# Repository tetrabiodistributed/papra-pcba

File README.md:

# PAPRA Printed Circuit Board Assembly (PCBA)

PAPRa PCBA - printed circuit board assembly for the PAPRa M12 Controller

Full documentation page for building the PAPRa can be found here: https://tetrabiodistributed.github.io/papra/

Firmware for flashing the PAPRA PCBA can be found here: https://github.com/tetrabiodistributed/papra-pcb-firmware/tree/main/papracode

## PAPRa PCBA comes in 2 form factors

### Thru Hole Technology

* Part Number A-TET-001113
* Suitable for hand soldering
* Larger form factor
* Easy to assemble, intended for novice 
* BOM parts should be easy to source
* Uses Adafruit QT PY or Seeed Xiao microcontroller board
* Firmware: TBD

### SMT

* Part Number A-TET-001100
* Suitable for mass production
* Smallest form factor
* Machine assembly recommended, very difficult to hand solder
* Lowest BOM cost
* Uses ATTINY 0/1/2-Series 14pin SOIC
* Firmware found here: https://github.com/tetrabiodistributed/papra-pcb-firmware/tree/main/papracode

## Notes for programming

* Make a UPDI Programmer: https://create.arduino.cc/projecthub/john-bradnam/create-your-own-updi-programmer-1e55f1?ref=user&ref_id=466812&offset=6
* The board features a UPDI header on the top left of the PCB (top being the side with the battery connectors) the pins are top to bottom 5V, GND and data. 
* Setup Arduino: https://www.hackster.io/john-bradnam/using-the-new-attiny-processors-with-arduino-ide-612185
* You will need to use the megaTinyCore library by SpenceKonde: https://github.com/SpenceKonde/megaTinyCore

Upload settings can be found in the arduino program. 

Please note that there are a number of ATTiny SKUs that are compatible with this PCB and code, please refer to the below table when choosing an appropriate IC.

| Model number   | Confirmed   | Notes                             |
| -------------- | ----------- | --------------------------------- |
| ATtiny204SSN_, | Yes         | See Below(1)  |
| ATtiny404SSN_, | Yes         |    	                           |
| ATtiny804SSN_, | Yes         |                                   |
| ATtiny1604SSN_,| Yes         |    	                           |
| ATtiny214SSN_, | Yes         | See Below(1)  |
| ATtiny414SSN_, | Yes         |    	                           |
| ATtiny814SSN_, | Yes         |                                   |
| ATtiny1614SSN_,| Yes         |    	                           |
| ATtiny1624SSU, | Yes         |    	                           |

(1)ATtiny 204 and 214 have limited (2K) flash memory for program space, but the firmware can be made to fit by sacraficing the bootup LED sequence.

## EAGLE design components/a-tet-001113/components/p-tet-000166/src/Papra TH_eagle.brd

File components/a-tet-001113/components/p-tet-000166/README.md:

# P-TET-000166 — PAPRa M12 Controller PCB (through-hole)

## Files

| Path | What |
|---|---|
| `src/Papra TH_eagle.sch`, `src/Papra TH_eagle.brd` | Original Eagle 9.6.2 design. Source of truth for the migration. |
| `src/papra-pcb-th/` | KiCad 10 project **generated** from the Eagle files by `make import`. Do not hand-edit until the Eagle files are retired; regenerate instead. |
| `src/papra-pcb-th/papra-pcb-th.pretty/`, `papra-pcb-th.kicad_sym` | Project footprint/symbol libraries extracted from the Eagle design. |
| `src/papra-pcb-th/3d/` | Manufacturer STEP models (see `3d/SOURCES.md`). |
| `dist/Papra TH_eagle_2023-03-08.zip` | Gerbers Eagle produced for the fab run. The Gerber check compares against these. |
| `../../lcsc-parts.csv` | LCSC numbers looked up for the BOM MPNs (`make lcsc`). |

## How the migration is validated (`make check`, from the repo root)

1. **Board structure** (`checks/test_board.py`): every Eagle element is a KiCad footprint with the
   same value, position, side; every pad has the same position, drill and copper size; every
   net has the same pads; the GND pour survived.
2. **Schematic** (`checks/test_schematic.py`): KiCad's own netlister reproduces Eagle's nets pad
   for pad; ERC has no errors; KiCad's schematic-parity DRC agrees board with schematic; the
   board passes the design rules translated from Eagle's `.brd`.
3. **Fab output** (`checks/test_gerbers.py`): Gerbers plotted from the KiCad board are rendered
   and XOR-compared per layer against the 2023 Eagle Gerbers; the drill files must list
   identical holes. Overlays land in `build/p-tet-000166/render/diff-<layer>.png`.
4. **3D placement** (`checks/test_models.py`): every model is placed with KiCad's own model
   transform (`checks/model_geom.py`, the matrix chain from the 3D viewer, on the geometry
   KiCad loads from the STEP file) and must sit on its side of the board with only its pins
   through it, landing on its pads. Manufacturer parts are held to datasheet numbers in
   `checks/parts.py` `PLACEMENT` (height, pin length, footprint, which way it faces).
5. **Determinism** (`checks/test_project.py`): a re-import of unchanged sources gives
   byte-identical files. kicad-cli and pcbnew mint random UUIDs and write elements in memory
   order; `checks/stable_ids.py` renames UUIDs by ordinal and sorts the board's blocks.

Known, accepted differences are listed in `checks/config.py` and `checks/project.py`.

## Regenerating

```
make import     # Eagle -> KiCad (board via kicad-cli, schematic via checks/sch_convert.py)
make check
make outputs    # ERC/DRC reports, PDFs, BOMs, Gerbers, drills, STEP, renders in build/
```

## Working in the KiCad GUI

- Open `src/papra-pcb-th/papra-pcb-th.kicad_pro`, not the `.kicad_sch` or `.kicad_pcb` on
  their own. The project carries the symbol/footprint library tables and the DRC/ERC
  severities; opened standalone, KiCad reports every library as missing and uses its
  default rules.
- Close KiCad before `make import`. KiCad keeps the project settings in memory and writes
  them back on save, which silently reverts the generated `.kicad_pro`.

## Additions over the Eagle design

- **Plated slots for the DC jack.** Eagle emulated the PJ-066A blade slots with pads, end
  holes and milling; the KiCad board has one plated oval pad per blade (`checks/parts.py`
  `SLOT_PADS`), which is what the fab produces and what DRC can reason about.
- **QR code on the bottom silkscreen** linking to https://tetrab.io, generated by
  `checks/qr.py` (content and module size in `checks/parts.py`) and placed automatically in
  the largest area free of holes, pads and other silkscreen. It is excluded from the Gerber
  comparison against the 2023 Eagle output, as are the slot pads.
- **3D models.** Standard parts use the models shipped with KiCad. The FASTON tabs, BNC,
  potentiometer and XIAO use manufacturer STEP files under `src/papra-pcb-th/3d/`
  (`3d/SOURCES.md`); their rotation and offset were solved, not eyeballed, by
  `checks/model_solve.py` from the model geometry and the datasheet rules, and are pinned in
  `checks/models.py`. The DC jack is drawn with KiCad's PJ-063AH model because Same Sky
  publishes none for the PJ-066A. To re-solve after changing a model or a rule:

  ```
  .venv/bin/python -m checks.model_solve POT1 H2 BATT+0 U1
  ```

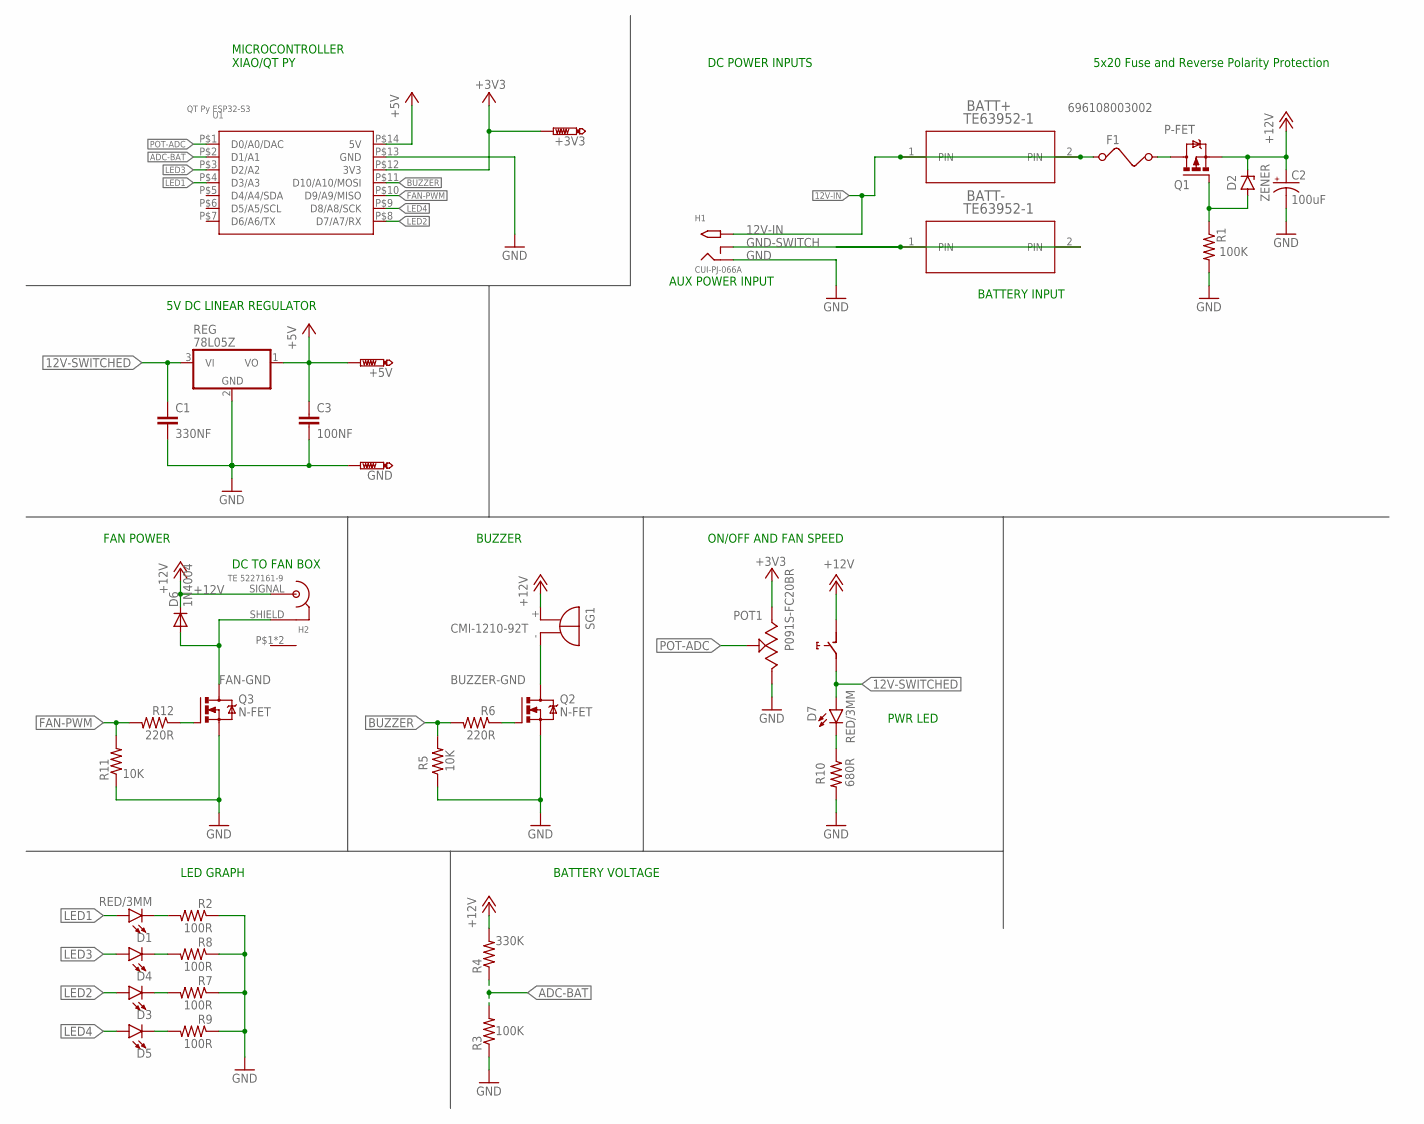
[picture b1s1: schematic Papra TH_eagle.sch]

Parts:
+3V3, +5V: PTR1PAD1-17; P1-17
BATT+: TE63952-1
BATT-: TE63952-1
C1: 330NF; CAP-PTH-SMALL-KIT
C2: 100uF; CPOL-RADIAL-2.5MM-6.5MM
C3: 100NF; CAP-PTH-SMALL-KIT
D1, D3, D4, D5, D7: RED/3MM; LED_3MM
D2: ZENER; DIODE-AXIAL
D6: 1N4004; DO41-10
F1: 696108003002; FUSE
GND: PTR1PAD1-17; P1-17
H1: CUI-PJ-066A; DCJACK-PJ-066A-SLOT
H2: TE 5227161-9; TE-BNC
POT1: P091S-FC20BR
Q1: P-FET; TO220BV
Q2, Q3: N-FET; TO220BV
R1, R3: 100K; 0207/10
R2, R7, R8, R9: 100R; 0207/10
R4: 330K; 0207/10
R5, R11: 10K; 0207/10
R6, R12: 220R; 0207/10
R10: 680R; 0207/10
REG: 78L05Z; TO92
SG1: CMI-1210-92T; F/TMB
U1: QT Py ESP32-S3; MODULE14P-TH+PAD

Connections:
12V-IN: BATT+.1, BATT+.2, F1.1, H1.PWR (TIP), H1.PWR$1 (TIP), H1.PWR$2 (TIP), H1.PWR$3 (TIP)
12V-IN-FUSED: F1.2, Q1.D
12V-IN-GATE: D2.1 (A), Q1.G, R1.1
12V-SWITCHED: C1.1, D7.A, POT1.NO (5), REG.3 (VI)
+3V3: +3V3.TP, POT1.3, U1.P$12 (3V3)
+5V: +5V.TP, C3.1, REG.1 (VO), U1.P$14 (5V)
+12V: C2.1 (+), D2.2 (C), D6.C, H2.SIGNAL (P1), POT1.COM (4), Q1.S, R4.2, SG1.+
ADC-BAT: R3.2, R4.1, U1.P$2 (D1/A1)
BUZZER: R5.2, R6.2, U1.P$11 (D10/A10/MOSI)
BUZZER-GND: Q2.D, SG1.-
FAN-GND: D6.A, H2.SHIELD (P2), Q3.D
FAN-PWM: R11.2, R12.2, U1.P$10 (D9/A9/MISO)
FETGATE: Q3.G, R12.1
FETGATE1: Q2.G, R6.1
GND: C1.2, C2.2 (-), C3.2, GND.TP, H1.GND (RING), H1.GND$1 (RING), H1.GND$2 (RING), H1.GND$3 (RING), POT1.1, Q2.S, Q3.S, R1.2, R2.1, R3.1, R5.1, R7.1, R8.1, R9.1, R10.2, R11.1, REG.2 (GND), U1.P$13 (GND)
GND-SWITCH: BATT-.1, BATT-.2, H1.GNDBREAK (RING_SW), H1.GNDBREAK$1 (RING_SW), H1.GNDBREAK$2 (RING_SW), H1.GNDBREAK$3 (RING_SW)
LED1: D1.A, U1.P$4 (D3/A3)
LED1.R: D1.K (C), R2.2
LED2: D3.A, U1.P$8 (D7/A7/RX)
LED2.R: D4.K (C), R8.2
LED3: D4.A, U1.P$3 (D2/A2)
LED3.R: D3.K (C), R7.2
LED4: D5.A, U1.P$9 (D8/A8/SCK)
LED4.R: D5.K (C), R9.2
LED5-R: D7.K (C), R10.1
POT-ADC: POT1.2, U1.P$1 (D0/A0/DAC)

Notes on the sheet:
AUX POWER INPUT
BATTERY INPUT
5x20 Fuse and Reverse Polarity Protection
5V DC LINEAR REGULATOR
ON/OFF AND FAN SPEED
FAN POWER
MICROCONTROLLER XIAO/QT PY
LED GRAPH
BATTERY VOLTAGE
DC TO FAN BOX
PWR LED
BUZZER
DC POWER INPUTS

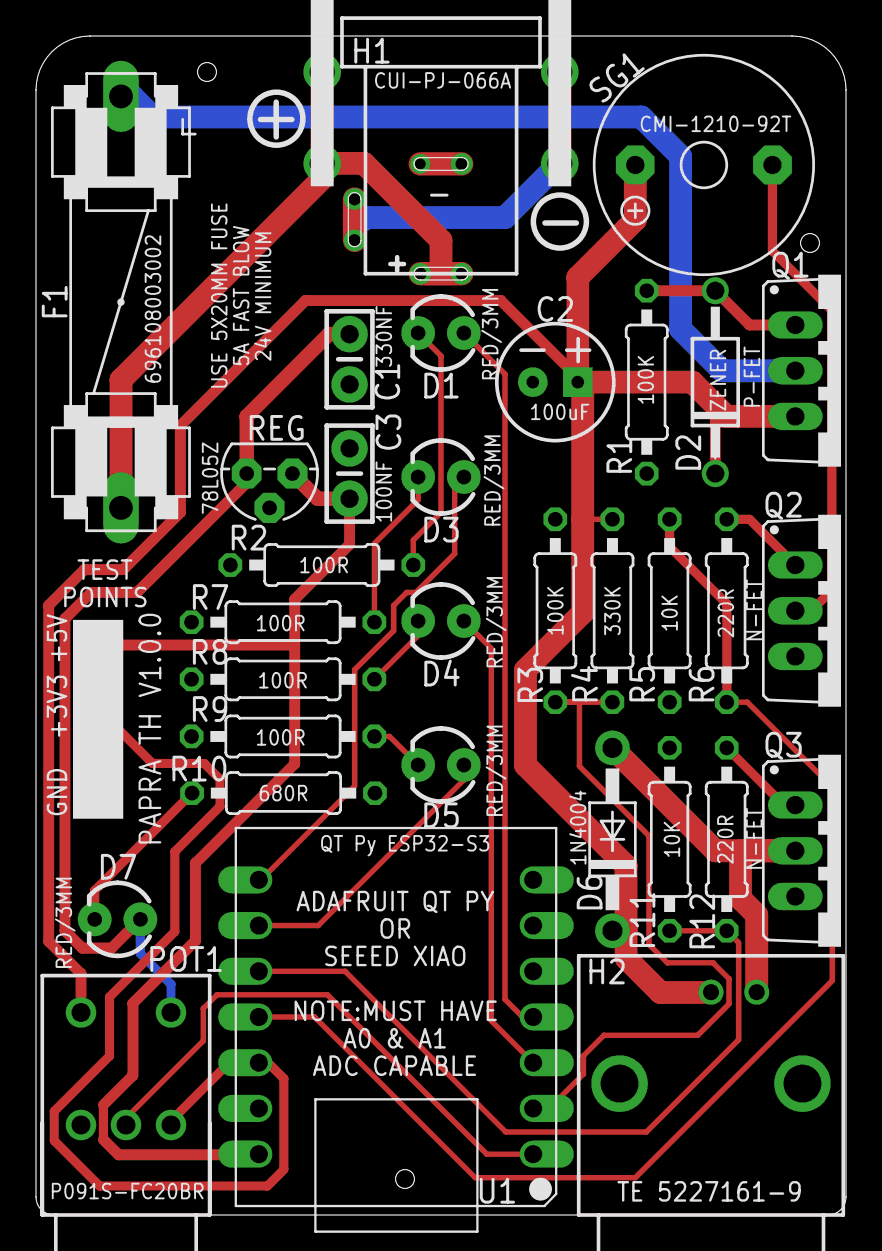
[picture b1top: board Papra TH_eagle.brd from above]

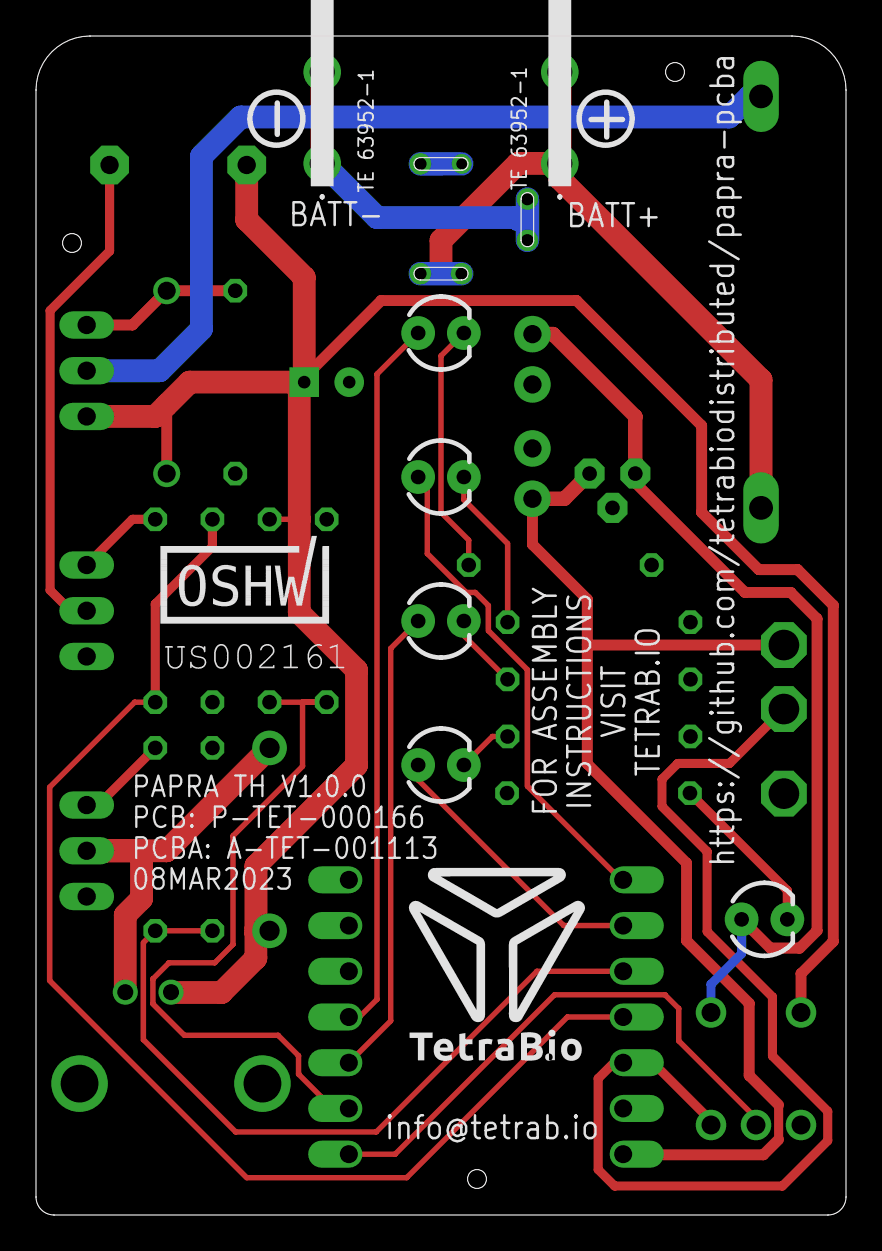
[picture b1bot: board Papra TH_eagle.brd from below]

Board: 2 copper layers, 45.0 x 65.5 mm, 37 parts (2 on the bottom side), 26 nets.

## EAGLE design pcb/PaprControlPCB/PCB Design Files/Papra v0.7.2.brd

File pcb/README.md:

The Tetra PAPRA project requires 1 PCBA, v.7 or newer.

PaprControlPCB - this is a speed controller that allows for adjusting speed of blower

Note:
A PCB is a bare board.
A PCBA is an assembly of a PCB and OTS (off the shelf) components, which are typically a mix of surface mount and thru-hole components.

PCBA Bring-Up Instructions:

1. Connect power to the board via 2.5mm DC jack (H1) using 12V Nominal (7V min, 14V max) DC power, ideally current limitable. Do not connect fan to the output connector at this time.

* Note DC polarity on connector is important, center pin is positive.
   * Insertion length on connector is 8.4mm, so body of mating jack should be at least this length.
   * For use with a bench power supply, a cut-end cable option is [Tensility CA-2185](https://www.digikey.com/en/products/detail/tensility-international-corp/CA-2185/568576) 
   * For a standalone power adapter, consider a [Tri-Mag L6R06H-120 12V/6W supply](https://www.digikey.com/en/products/detail/tri-mag-llc/L6R06H-120/7682617)
2. For adjustable power supply, set the voltage to12V and set initial current limit to ~25mA, which should be sufficient to power up processor and drive LEDs.
3. Turn the potentiometer/switch (POT1) to ON. 

4. Confirm the power LED (LED5) illuminates with 12V power.

5. Measure 5V regulator (U1) is outputting 5VDC. This can be inspected with a voltmeter measuring the UDPI header as follows:
   * Pin 2 is GND
   * Pin 3 is +5V
6. At this point, the board is powered and ready for programming via UPDI. Follow the instructions [here.](https://github.com/tetrabiodistributed/PAPRA-PCB/blob/main/README.md).
7. Upon successful completion of firmware installation, confirm the board powers up and the 4 LEDs (LED1 - LED4) light up at boot up in a sequence.
8. For boards with the buzzer installed, confirm the buzzer chirps at bootup.
9. In preparation for testing with a DC blower and battery, disconnect the DC jack from H1.
10. Source a fully charged [Milwaukee M12 Red Lithium Battery 48-11-2401](https://www.milwaukeetool.com/Products/Batteries-and-Chargers/M12-Batteries-and-Chargers/48-11-2401) or similar. 
11. Connect DC power to BNC connector (H2).
* WARNING: If the board is not installed in the battery housing, pay careful attention to the polarity
12. Turn on potentiometer (POT1) and adjust the fan speed from high to low, which checking the DC blower is working and speed is changing with potentiometer adjustments.

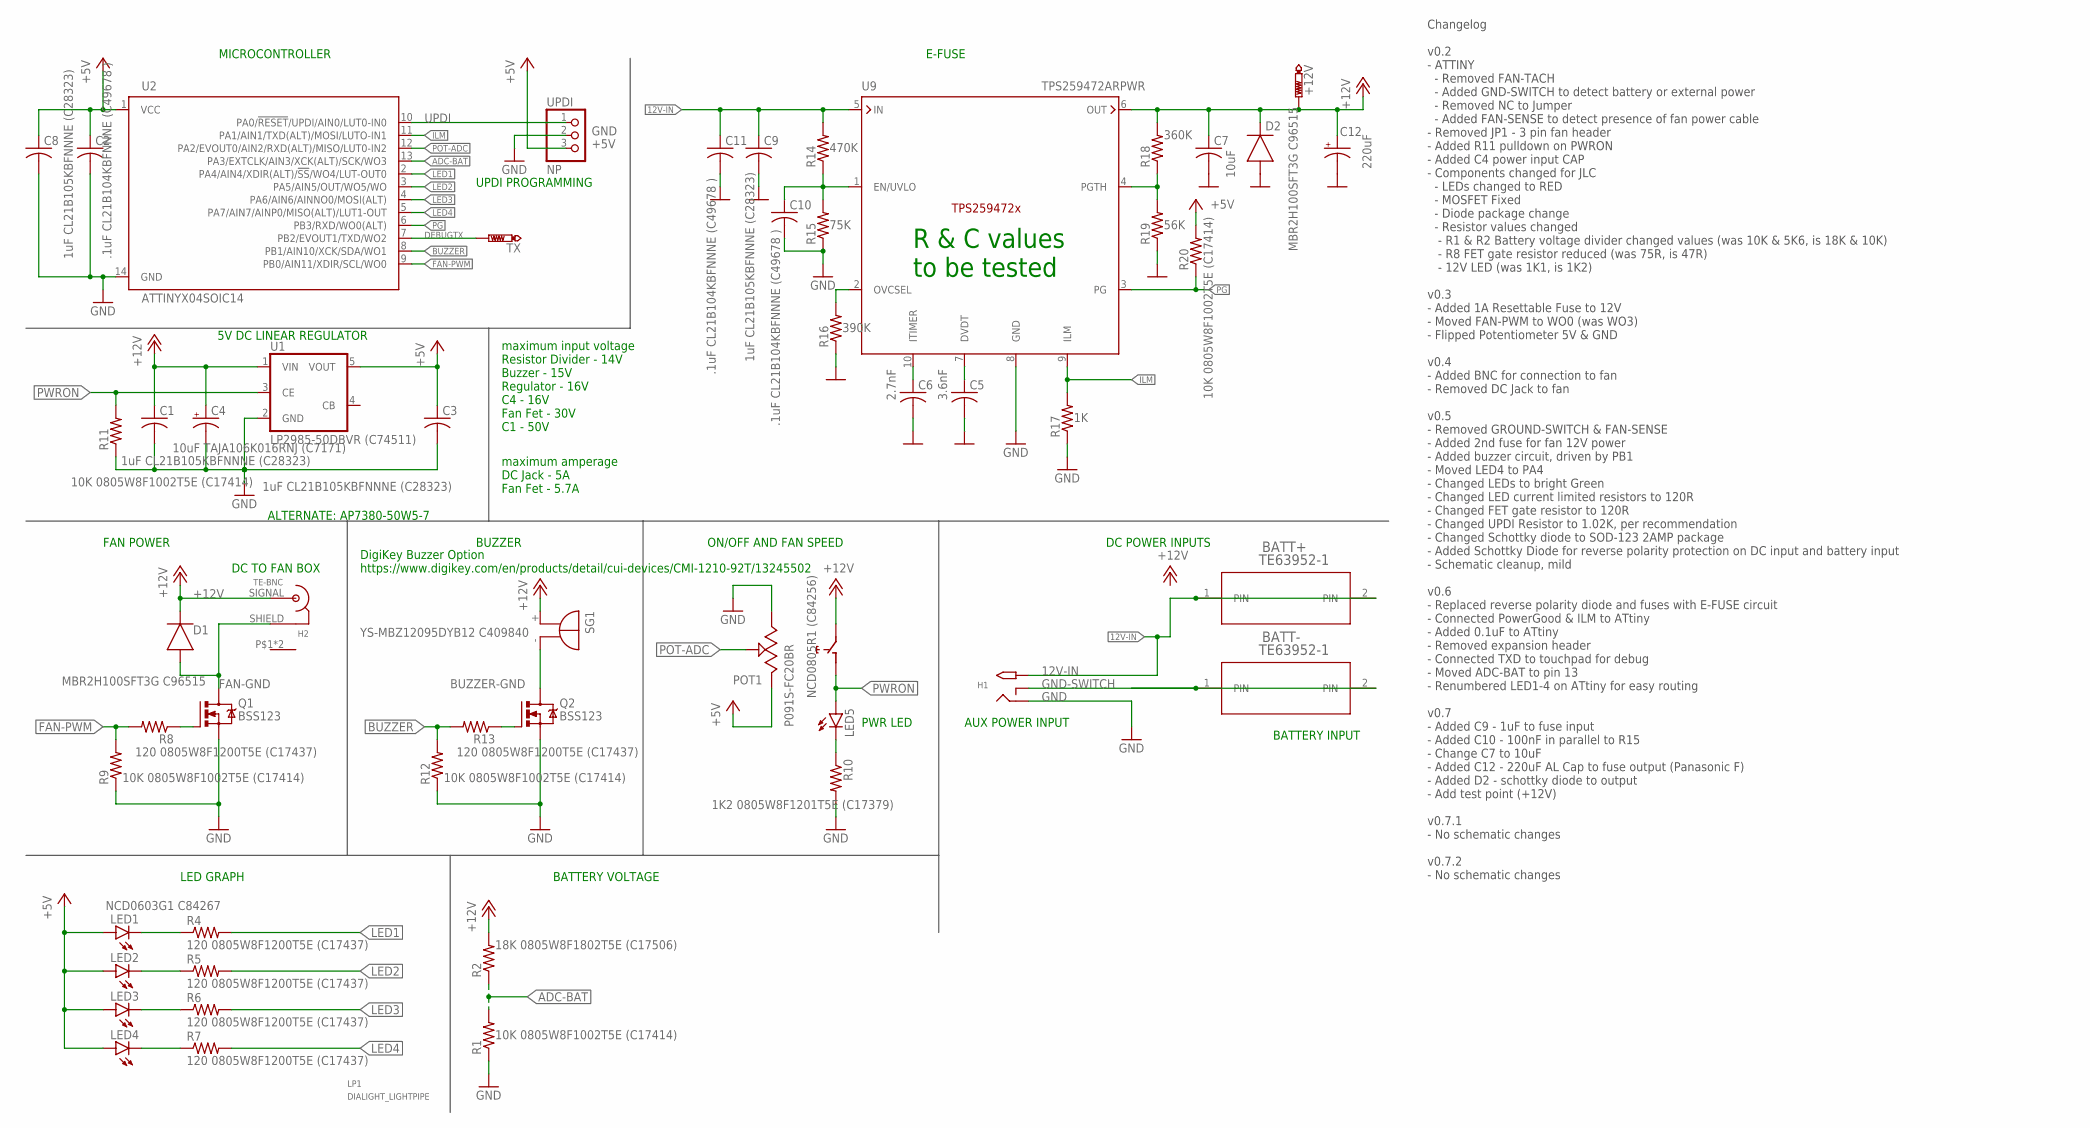
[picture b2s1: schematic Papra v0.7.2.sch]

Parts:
+12V: PTR1B1,27; B1,27
BATT+: TE63952-1
BATT-: TE63952-1
C1, C3, C8, C11: 1uF CL21B105KBFNNNE (C28323); C0805
C2, C9, C10: .1uF CL21B104KBFNNNE (C49678 ); C0805
C4: 10uF TAJA106K016RNJ (C7171); A/3216-18R
C5: 3.6nF; C0805
C6: 2.7nF; C0805
C7: 10uF; C0805
C12: 220uF; PANASONIC_F
D1, D2: MBR2H100SFT3G C96515; SODFL3718X115
H1: M-CUI-PJ-066A; DCJACK-PJ-066A
H2: TE-BNC
LED1, LED2, LED3, LED4: NCD0603G1 C84267; CHIPLED_0805
LED5: NCD0805R1 (C84256); CHIPLED_0805
LP1: DIALIGHT_LIGHTPIPE; DIALIGHT_5151020F_/LEDS
POT1: P091S-FC20BR
Q1, Q2: BSS123; SOT23
R1, R9, R11, R12, R20: 10K 0805W8F1002T5E (C17414); R0805
R2: 18K 0805W8F1802T5E (C17506); R0805
R4, R5, R6, R7, R8, R13: 120 0805W8F1200T5E (C17437); R0805
R10: 1K2 0805W8F1201T5E (C17379); R0805
R14: 470K; R0805
R15: 75K; R0805
R16: 390K; R0805
R17: 1K; R0805
R18: 360K; R0805
R19: 56K; R0805
SG1: YS-MBZ12095DYB12 C409840; F/TMB
TX: PTR1PAD1-13; P1-13
U1: LP2985-50DBVR (C74511); SOT25
U2: ATTINYX04SOIC14; SOIC127P600X144-14
U9: TPS259472ARPWR; QFN45P200X200X100-16N
UPDI: NP; 1X03

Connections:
12V-IN: BATT+.1, BATT+.2, C9.1, C11.1, H1.PWR (TIP), R14.2, U9.5 (IN)
+5V: C2.1, C3.1, C8.1, LED1.A, LED2.A, LED3.A, LED4.A, POT1.3, R20.2, U1.5 (VOUT), U2.1 (VCC), UPDI.3
+12V: +12V.TP, C1.1, C4.+, C7.1, C12.+, D1.1 (C), D2.1 (C), H2.SIGNAL (P1), POT1.NO (5), R2.2, R18.2, SG1.+, U1.1 (VIN), U9.6 (OUT)
ADC-BAT: R1.2, R2.1, U2.13 (PA3/EXTCLK/AIN3/XCK(ALT)/SCK/WO3)
BUZZER: R12.2, R13.2, U2.8 (PB1/AIN10/XCK/SDA/WO1)
BUZZER-GND: Q2.3 (D), SG1.-
DEBUGTX: TX.TP, U2.7 (PB2/EVOUT1/TXD/WO2)
DVDT: C5.1, U9.7 (DVDT)
EN/UVLO: C10.1, R14.1, R15.2, U9.1 (EN/UVLO)
FAN-GND: D1.2 (A), H2.SHIELD (P2), Q1.3 (D)
FAN-PWM: R8.2, R9.2, U2.9 (PB0/AIN11/XDIR/SCL/WO0)
FETGATE: Q1.1 (G), R8.1
FETGATE1: Q2.1 (G), R13.1
GND: C1.2, C2.2, C3.2, C4.-, C5.2, C6.2, C7.2, C8.2, C9.2, C10.2, C11.2, C12.-, D2.2 (A), H1.GND (RING), POT1.1, Q1.2 (S), Q2.2 (S), R1.1, R9.1, R10.2, R11.1, R12.1, R15.1, R16.1, R17.1, R19.1, U1.2 (GND), U2.14 (GND), U9.8 (GND), UPDI.2
GND-SWITCH: BATT-.1, BATT-.2, H1.GNDBREAK (RING_SW)
ILM: R17.2, U2.11 (PA1/AIN1/TXD(ALT)/MOSI/LUTO-IN1), U9.9 (ILM)
ITIMER: C6.1, U9.10 (ITIMER)
LED1: R4.2, U2.2 (PA4/AIN4/XDIR(ALT)/!SS!/WO4/LUT-OUT0)
LED1-R: LED1.C, R4.1
LED2: R5.2, U2.3 (PA5/AIN5/OUT/WO5/WO)
LED2-R: LED2.C, R5.1
LED3: R6.2, U2.4 (PA6/AIN6/AINNO0/MOSI(ALT))
LED3-R: LED3.C, R6.1
LED4: R7.2, U2.5 (PA7/AIN7/AINP0/MISO(ALT)/LUT1-OUT)
LED4-R: LED4.C, R7.1
LED5-R: LED5.C, R10.1
OVCSEL: R16.2, U9.2 (OVCSEL)
PG: R20.1, U2.6 (PB3/RXD/WO0(ALT)), U9.3 (PG)
PGTH: R18.1, R19.2, U9.4 (PGTH)
POT-ADC: POT1.2, U2.12 (PA2/EVOUT0/AIN2/RXD(ALT)/MISO/LUT0-IN2)
PWRON: LED5.A, POT1.COM (4), R11.2, U1.3 (CE)
UPDI: U2.10 (PA0/!RESET!/UPDI/AIN0/LUT0-IN0), UPDI.1

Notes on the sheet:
AUX POWER INPUT
BATTERY INPUT
E-FUSE
5V DC LINEAR REGULATOR
ON/OFF AND FAN SPEED
FAN POWER
MICROCONTROLLER
LED GRAPH
BATTERY VOLTAGE
DC TO FAN BOX
UPDI PROGRAMMING
PWR LED
ALTERNATE: AP7380-50W5-7
Changelog v0.2 - ATTINY - Removed FAN-TACH - Added GND-SWITCH to detect battery or external power - Removed NC to Jumper - Added FAN-SENSE to detect presence of fan power cable - Removed JP1 - 3 pin fan header - Added R11 pulldown on PWRON - Added C4 power input CAP - Components changed for JLC - L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
BUZZER
maximum input voltage Resistor Divider - 14V Buzzer - 15V Regulator - 16V C4 - 16V Fan Fet - 30V C1 - 50V
maximum amperage DC Jack - 5A Fan Fet - 5.7A
DigiKey Buzzer Option https://www.digikey.com/en/products/detail/cui-devices/CMI-1210-92T/13245502
DC POWER INPUTS
R & C values to be tested

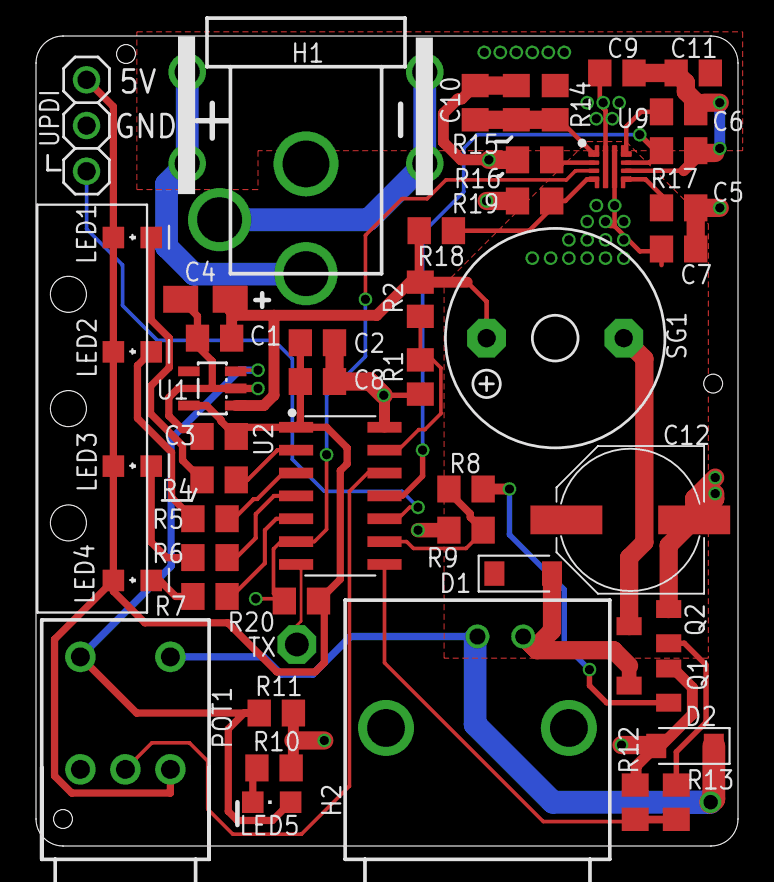
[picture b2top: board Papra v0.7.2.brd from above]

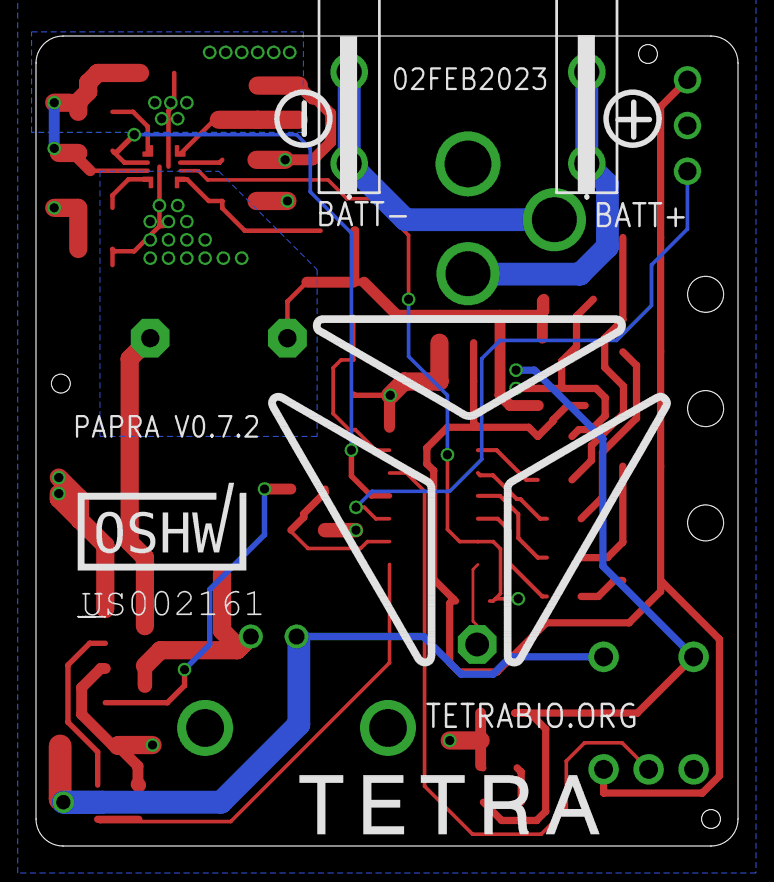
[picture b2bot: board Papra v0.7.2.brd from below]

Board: 2 copper layers, 39.0 x 45.0 mm, 53 parts (3 on the bottom side), 32 nets.

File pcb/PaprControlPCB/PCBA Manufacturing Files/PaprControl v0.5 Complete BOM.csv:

Surface Mount Components,,,,,,,,
,Qty,Designator,Value,Manufacturer,Manufacturer's Part #,Package,Vendor,Vendor Part #
,2,C1 C3,1uF ,Samsung,CL21B105KBFNNNE ,C0805,LCSC,C28323
,1,C2,.1uF,YAGEO ,CC0805KRX7R9BB104,C0805,LCSC,C49678
,1,C4,10uF,AVX,TAJA106K016RNJ,CASE0A_3216,LCSC,C7171
,3,D1 D2 D3,SCHOTTKY 100V 2A,ON Semiconductor,MBR2H100SFT3G,SOD-123,LCSC,C96515
,2,F1 F2,Polyfuse 13.2V 1.8A,Techfuse,nSMD100-13.2V,1206,LCSC,C70081
,4,LED1 LED2 LED3 LED4,"Grn LED, Superbright",Foshan,NCD0805G1,805,LCSC,C84260
,1,LED5,Red LED,Foshan,NCD0805R1,805,LCSC,C84256
,2,"Q1,Q2","MOSFET, N-Channel 30V 5.7A ",Alpha & Omega,AO3400A,SOT-23-3L,LCSC,C20917
,4,R1 R9 R11 R12,10K,Uni-Royal,0805W8F1002T5E,805,LCSC,C17414
,1,R2,18K,Uni-Royal,0805W8F1802T5E,805,LCSC,C17506
,2,R3 R10,1.2K,Uni-Royal,0805W8F1201T5E,805,LCSC,C17379
,6,R4 R5 R6 R7 R8 R13,120R,Uni-Royal,0805W8F1200T5E,805,LCSC,C17437
,1,U1,"LDO, Fixed 5V 150mA",Texas Instruments,LP2985-50DBVR,SOT-23-5,LCSC,C74511
,1,U2,ATtiny AVR,Microchip,ATTINY1614-SSNR,SOIC-14,LCSC,C481364
,,,,,,,,
Thru-Hole Components,,,,,,,,
,Qty,Designator,Value,Manufacturer,Manufacturer's Part #,Package,Vendor,Vendor Part #
,2,"BATT+, BATT-",Battery Tabs,TE Connectivity,1217754-1,,Digikey,A112005-ND
,1,H1,2.1 x 5.5mm DC Jack,CUI,PJ-066A,,Digikey,CP-066A-ND
,1,H2,BNC,TE,5227161-9,,Digikey,A32261-ND
,1,POT1,Pot w/switch,TT Electronics,P091S-FC20BR10K,,Digikey,987-1283-ND
,1,SG1,"Buzzer, 12 mm x 9.5 mm",CUI,CMI-1295-1285T,,Digikey,102-CMI-1295-1285T-ND
,1,LP1,Quad Lightpipe,DIALIGHT,5151020F,,Digikey,350-2166-ND
,,,,,,,,
,1,H3,DO NOT POPULATE,,,,,
,1,UPDI,DO NOT POPULATE,,,,,

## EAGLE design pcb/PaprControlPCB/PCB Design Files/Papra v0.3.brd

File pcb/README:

The Teta PAPRA project requires 1 PCBAs for v.7

PaprControlPCB - this is a speed controller that allows for adjusting speed of blower

Note:
A PCB is a bare board.
A PCBA is an assembly of a PCB and OTS (off the shelf) components, which are typically a mix of surface mount and thru-hole components.

Board Bring Up Instructions:

1. Connect power to the board via 2.5mm DC jack(H1) using 12V Nominal (7V min, 14V max) DC power, ideally current limitable. Do not connect to fan output.
   A. Note polarity on connector is important, center pin is positive.
   B. Insertion length on connector is 8.4mm, so body of mating jack should be at least this length.
   C. For use with a bech power supply, a cut-end cable option is [Tensility CA-2185](https://www.digikey.com/en/products/detail/tensility-international-corp/CA-2185/568576)
   D. For a standalone power adapter, consier a (Tri-Mag L6R06H-120 12V/6W supply)[https://www.digikey.com/en/products/detail/tri-mag-llc/L6R06H-120/7682617]
2. For adjustable power supply, set initial current limit to 50mA, which should be sufficient to power up processor and drive LEDs.
3. Turn the potentiomenter/swith (POT1) to ON. 
4. Notice the power LED (LED5) light up with 12V power.
5. Measure 5V regulator (U1) is outputting 5VDC. This can be inspected with a voltmeter measuring the UDPI header as follows:
   A. Pin 2 is GND
   B. Pin 3 is +5V
6. At this point, the board is powered and ready for programming via UPDI. Follow the instructions [here.](https://github.com/tetrabiodistributed/PAPRA-PCB/blob/main/README.md)
7. Upon successful completion of firmware installation, confirm the board powers up and the 4 LEDs (LED1 - LED4) light up at boot up in a sequence.
8. For boards with the buzzer installed, confirm the buzzer chirps at bootup.
9. In preparation for testing with a DC blower, power the board using the battery tabs and connecting to a (Milwaukee M12 Red Lithium Battery, 48-11-2401)[https://www.milwaukeetool.com/Products/Batteries-and-Chargers/M12-Batteries-and-Chargers/48-11-2401] or similar. 
   A. WARNING: If the board is not installed in the battery housing, pay careful attention to the polarity
10. Connect DC power to BNC connector (H2)
11. Turn on potentiomenter (POT1) and adjust the fan speed from high to low, which checking the DC blower is working and speed is changing with potentiometer adjustments

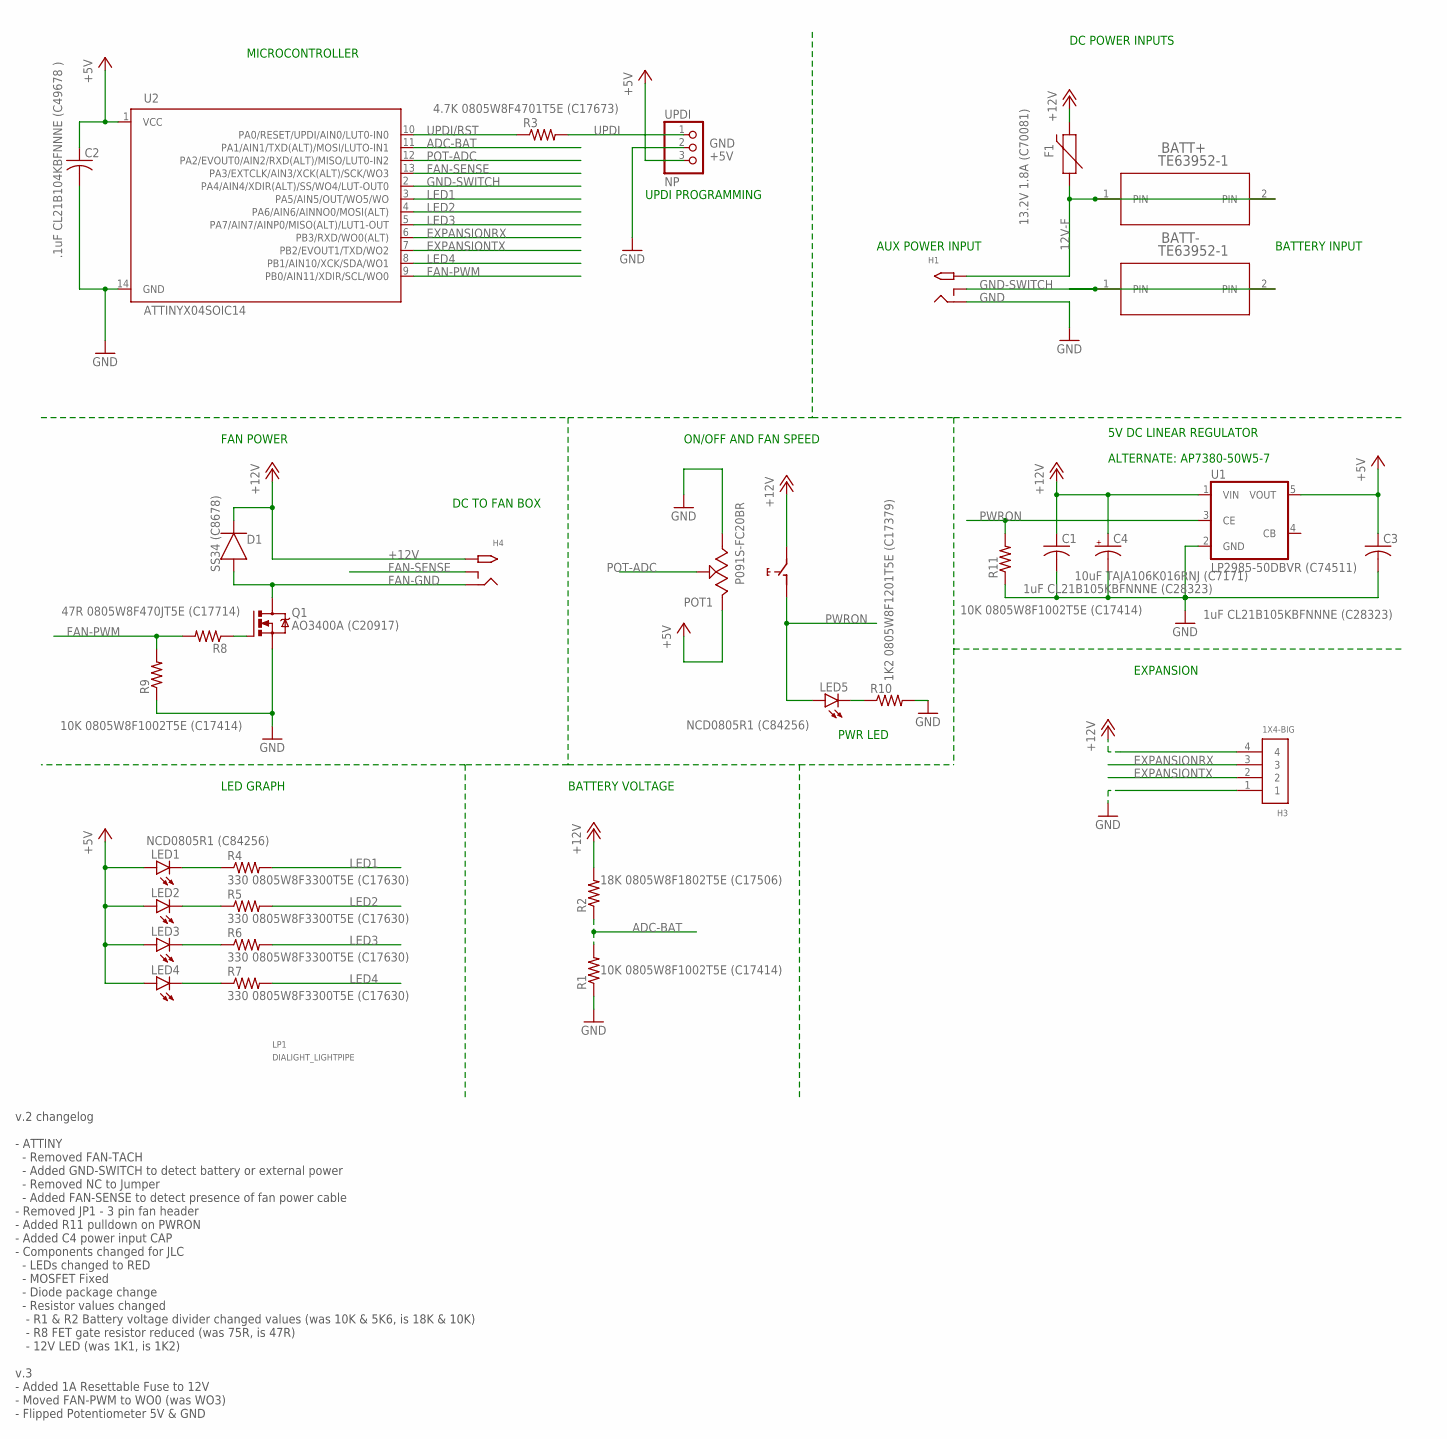
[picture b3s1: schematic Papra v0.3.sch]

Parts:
BATT+: TE63952-1
BATT-: TE63952-1
C1, C3: 1uF CL21B105KBFNNNE (C28323); C0805
C2: .1uF CL21B104KBFNNNE (C49678 ); C0805
C4: 10uF TAJA106K016RNJ (C7171); A/3216-18R
D1: SS34 (C8678); DIOM5226X290N
F1: 13.2V 1.8A (C70081); 1206
H1, H4: M-CUI-PJ-066A; DCJACK-PJ-066A
H3: 1X4-BIG; 1X04-BIG
LED1, LED2, LED3, LED4, LED5: NCD0805R1 (C84256); CHIPLED_0805
LP1: DIALIGHT_LIGHTPIPE; DIALIGHT_5151020F_/LEDS
POT1: P091S-FC20BR
Q1: AO3400A (C20917); SOT23
R1, R9, R11: 10K 0805W8F1002T5E (C17414); R0805
R2: 18K 0805W8F1802T5E (C17506); R0805
R3: 4.7K 0805W8F4701T5E (C17673); R0805
R4, R5, R6, R7: 330 0805W8F3300T5E (C17630); R0805
R8: 47R 0805W8F470JT5E (C17714); R0805
R10: 1K2 0805W8F1201T5E (C17379); R0805
U1: LP2985-50DBVR (C74511); SOT25
U2: ATTINYX04SOIC14; SOIC127P600X144-14
UPDI: NP; 1X03

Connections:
12V-F: BATT+.1, BATT+.2, F1.1, H1.PWR (TIP)
+5V: C2.1, C3.1, LED1.A, LED2.A, LED3.A, LED4.A, POT1.3, U1.5 (VOUT), U2.1 (VCC), UPDI.3
+12V: C1.1, C4.+, D1.1 (C), F1.2, H3.4, H4.PWR (TIP), POT1.NO (5), R2.2, U1.1 (VIN)
ADC-BAT: R1.2, R2.1, U2.11 (PA1/AIN1/TXD(ALT)/MOSI/LUTO-IN1)
EXPANSIONRX: H3.3, U2.6 (PB3/RXD/WO0(ALT))
EXPANSIONTX: H3.2, U2.7 (PB2/EVOUT1/TXD/WO2)
FAN-GND: D1.2 (A), H4.GND (RING), Q1.3 (D)
FAN-PWM: R8.2, R9.2, U2.9 (PB0/AIN11/XDIR/SCL/WO0)
FAN-SENSE: H4.GNDBREAK (RING_SW), U2.13 (PA3/EXTCLK/AIN3/XCK(ALT)/SCK/WO3)
FETGATE: Q1.1 (G), R8.1
GND: C1.2, C2.2, C3.2, C4.-, H1.GND (RING), H3.1, POT1.1, Q1.2 (S), R1.1, R9.1, R10.2, R11.1, U1.2 (GND), U2.14 (GND), UPDI.2
GND-SWITCH: BATT-.1, BATT-.2, H1.GNDBREAK (RING_SW), U2.2 (PA4/AIN4/XDIR(ALT)/SS/WO4/LUT-OUT0)
LED1: R4.2, U2.3 (PA5/AIN5/OUT/WO5/WO)
LED1-R: LED1.C, R4.1
LED2: R5.2, U2.4 (PA6/AIN6/AINNO0/MOSI(ALT))
LED2-R: LED2.C, R5.1
LED3: R6.2, U2.5 (PA7/AIN7/AINP0/MISO(ALT)/LUT1-OUT)
LED3-R: LED3.C, R6.1
LED4: R7.2, U2.8 (PB1/AIN10/XCK/SDA/WO1)
LED4-R: LED4.C, R7.1
LED5-R: LED5.C, R10.1
POT-ADC: POT1.2, U2.12 (PA2/EVOUT0/AIN2/RXD(ALT)/MISO/LUT0-IN2)
PWRON: LED5.A, POT1.COM (4), R11.2, U1.3 (CE)
UPDI: R3.2, UPDI.1
UPDI/RST: R3.1, U2.10 (PA0/RESET/UPDI/AIN0/LUT0-IN0)

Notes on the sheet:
AUX POWER INPUT
BATTERY INPUT
DC POWER INPUTS
5V DC LINEAR REGULATOR
ON/OFF AND FAN SPEED
FAN POWER
MICROCONTROLLER
LED GRAPH
BATTERY VOLTAGE
EXPANSION
DC TO FAN BOX
UPDI PROGRAMMING
PWR LED
ALTERNATE: AP7380-50W5-7
v.2 changelog - ATTINY - Removed FAN-TACH - Added GND-SWITCH to detect battery or external power - Removed NC to Jumper - Added FAN-SENSE to detect presence of fan power cable - Removed JP1 - 3 pin fan header - Added R11 pulldown on PWRON - Added C4 power input CAP - Components changed for JLC - LE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

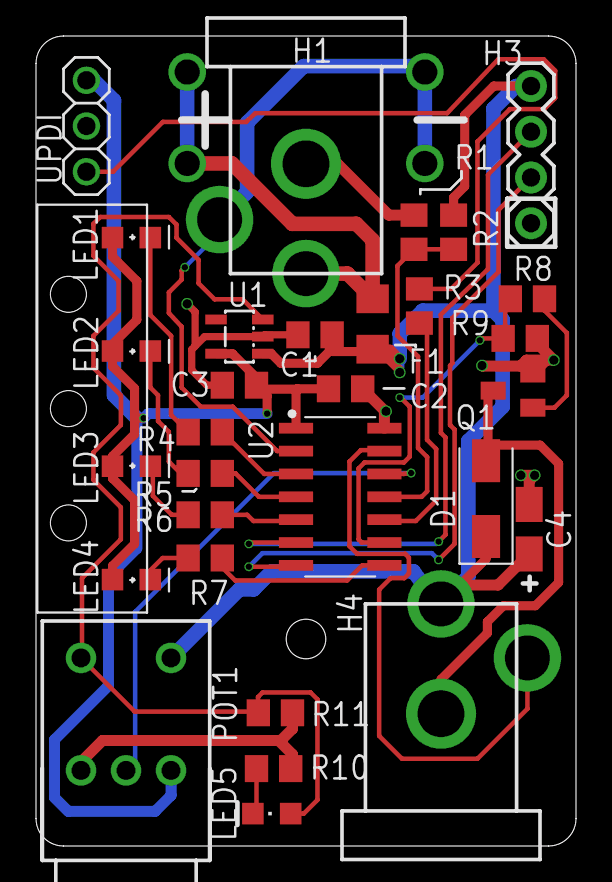
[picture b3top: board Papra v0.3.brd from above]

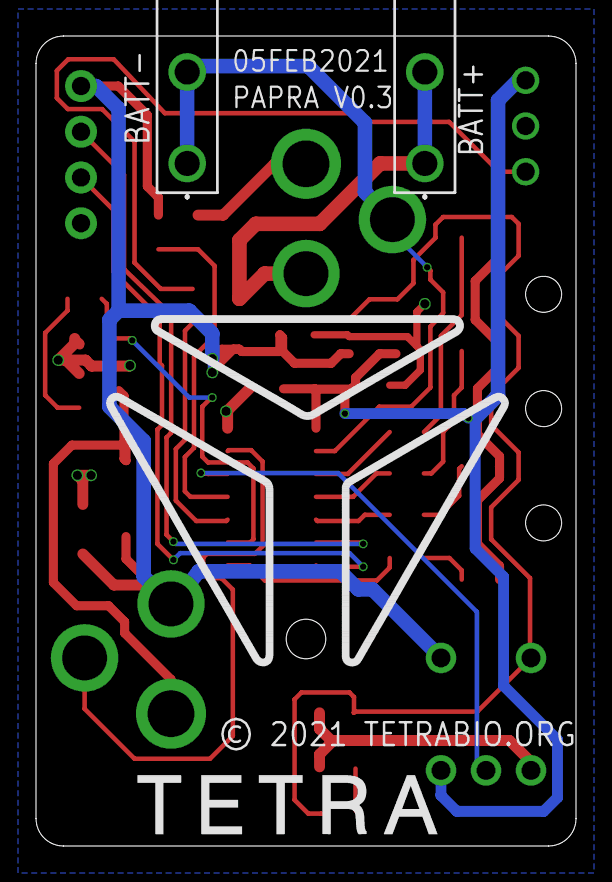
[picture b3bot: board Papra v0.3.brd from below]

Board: 2 copper layers, 30.0 x 45.0 mm, 33 parts (2 on the bottom side), 25 nets.

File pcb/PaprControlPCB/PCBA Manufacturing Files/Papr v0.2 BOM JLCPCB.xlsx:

Comment | Designator | Footprint | LCSC Part #（optional）
1uF | C1, C3 | C0805 | C28323
.1uF | C2 | C0805 | C49678
10uF | C4 | A/3216-18R | C7171
SS34 | D1 | DIOM5226X290N | C8678
NCD0805R1 | LED1, LED2, LED3, LED4, LED5 | CHIPLED_0805 | C84256
AO3400A | Q1 | SOT23 | C20917
10K | R1, R9, R11 | R0805 | C17414
18K | R2 | R0805 | C17506
4.7K | R3 | R0805 | C17673
330 | R4, R5, R6, R7 | R0805 | C17630
47R | R8 | R0805 | C17714
1K2 | R10 | R0805 | C17379
LP2985-50DBVR | U1 | SOT-25-5 | C74511

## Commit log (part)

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2020-11-20 Adding notes to readme
2020-11-20 readme
2020-11-24 Added fuel gauge LED code
2020-11-25 Added state machine for LEDs
2020-11-26 Implemented in PWM to prevent motor stalling at low end
2020-11-28 Added battery smoothing, fixed scaling formula. Tested
2020-12-11 PCB v0.2
2020-12-11 Adding pdf schematic
2020-12-20 adding newer setup image - Correcting Clock setting to 20 MHz
    was 16 MHz
2021-01-09 v0.2 PCB updates and knob speed reverse
2021-01-10 Switching to AtTiny1604 for codespace headroom
2021-01-11 Papra PCB Ready for release
2021-01-15 Updating the boards for the 3rd build
2021-01-19 Updates/Fixes to PCB and PCBA files.
    Added TETRA logo to bottom silk
2021-01-19 design files
2021-01-21 Added 1A resettable fuse to 12V power
2021-01-22 Added CERN 2.0 P License
2021-01-28 20kHz PWM freq (need to test)
2021-02-01 20kHz PWM with re-calibrated minimum PWM value
2021-02-05 v0.3 release candidate
2021-02-06 Reverting back to v0.2
2021-02-07 v0.3 pcb
2021-02-08 DRU update to latest
2021-02-15 Updated fan box PCB to v0.3 (IP68 DC Jack)
2021-02-22 STEP file update
2021-02-22 Adding in drawings for the PCBA
2021-02-26 fixing pin# mistake in code comments
2021-02-26 Update README.md
    Update README.md with compatability table for ATTiny SKUs.
2021-02-28 Updated SerialEvent note for memory constrained ICs
2021-02-28 Update README.md
    Adding comments for the pinout of the UPDI header.
2021-03-01 adding engineering drawings
2021-03-03 Updating drawings per Darragh, command line gitignore
2021-03-05 Update drawings for March 2021 release
2021-03-10 Update README.md
    Update with new arduino config
2021-03-24 v.4 board files, released batch of 3 to OSH
2021-03-28 adding .hex
2021-04-17 Chip confirmation update
2021-04-24 PAPRA Control PCB v0.4 design and manufacturing
    3 Boards have been made (Oshpark), just pushing the documentation as v0.5 is imminent.
    Consider v0.4 a test version
2021-04-24 Remove fan box board files and update firmware
    Fan box no longer has PCB
    Firmware needs to run for v.3 or later
2021-04-24 Adding schematic for review
2021-04-26 V.5 with PCB layout, for review
2021-04-26 Moved Buzzer to W01 & LED4 to PA4
2021-04-26 Releasing to OSH
    - Fixed for JLC DRU
    - Unused pin tied to via & labeled PA3
    - Adding 2 vias to allow shorting the UPDI resistor for use with programmers that have the UPDI in-circuit
    - Tied the posts on the BNC together (can't tie to ground as we are switching ground)
    - Silkscreen touchups
2021-05-09 v.5 pcb code
2021-05-13 Eagle DRU
2021-05-13 firmware for v0.3 PCB
2021-05-13 Update chip list
2021-05-13 Update README.md
    Removed image that is being deleted and added info on where upload settings can be found.
2021-05-13 Updating readme
    Added note about commenting out the LED startup sequence to fit in a 2K flash code space
2021-05-13 update note on ATtiny204SSN_
2021-05-15 Firmware in Submodule
2021-05-16 Updating PCBA Drawing
2021-05-22 File cleanup
    Adding in JLC production files, updated BOMs and resolved conflict
2021-05-22 Documentation updates
    -PDFs for board assembly & M12 controller assembly
    -Adding firmware to right location
    -PCB Step cad model
2021-05-24 V.5 Release candidate
2021-05-24 Readme Update
2021-05-24 Firmware moved to submodule
2021-05-24 adding firmware location in readme
2021-05-24 Drawing update
2021-05-31 Rotate drawing
2021-05-31 Rotate Drawing
    Should be right this time
2021-05-31 Title block update
2021-05-31 Title block & partlist update
2021-07-27 Board ready for review
    Closes #53
2021-07-28 Updates based on feedback
2021-09-06 Adding gerbers
2022-05-16 Updating to v0.7
    Closes #59
2022-05-27 Updated changelogs for schematic & PCB
2022-12-17 Rename README to README.md
2022-12-17 Update README.md
    Formatting
2023-01-31 Adding images and grammar cleanup/spelling
2023-01-31 Adding punctuation
2023-02-02 DFM Update
    Closes #72
    Closes #73
    Closes #74
2023-02-16 Adding thru hole schematic design
2023-02-25 Adding KiCad Schematic
2023-02-25 Adding the PCB file for mechanical
    Sized at 40mm wide, symmetric. Added 10mm to length
2023-02-26 rescaffold file structure as DOF-component
    as to be able to accommodate both surface mount and through hole assembly options
2023-02-26 delete pcb/README.md
    as it's been replaced by assemblySteps.yaml in a-tet-001100
2023-02-26 rename kicad files to be dash-separated-lowercase
2023-02-26 add kicad project file for papra-pcb-th
2023-02-26 move Papra TH Schematic PDF to dist/
2023-02-26 update kicad project file for papra-pcb-th
    as to be able to open pcb and schematic in kicad
2023-02-26 Adding eagle footprints
2023-02-26 The whole folder
2023-02-26 attempting to resolve footprints
2023-03-03 update project name to papra-pcba
2023-03-03 move D-TET-001100-2 PDF to its dist/ directory
2023-03-08 Adding eagle design files, BOM and updating readme
2023-03-08 Ready for production - adding gerbers and final PCB design files
2023-03-13 Updated BOM
2023-04-30 correction on 10k
2023-04-30 Cleanup on resistors
    Changed to 1% tolerance
    Adding resistor manufacturer, manufacturer part number and description
2024-04-06 update README with link to papra documentaiton page
2025-03-29 remove out-of-date kicad files
2025-03-29 add updated kicad files for thruhole board imported from eagle

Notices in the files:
pcb/PaprControlPCB/PCB Design Files/Papra v0.3.brd:
© 2021 TETRABIO.ORG
parts and their libraries:
SparkFun-LED: Licensing: Creative Commons ShareAlike 4.0 International - https://creativecommons.org/licenses/by-sa/4.0
